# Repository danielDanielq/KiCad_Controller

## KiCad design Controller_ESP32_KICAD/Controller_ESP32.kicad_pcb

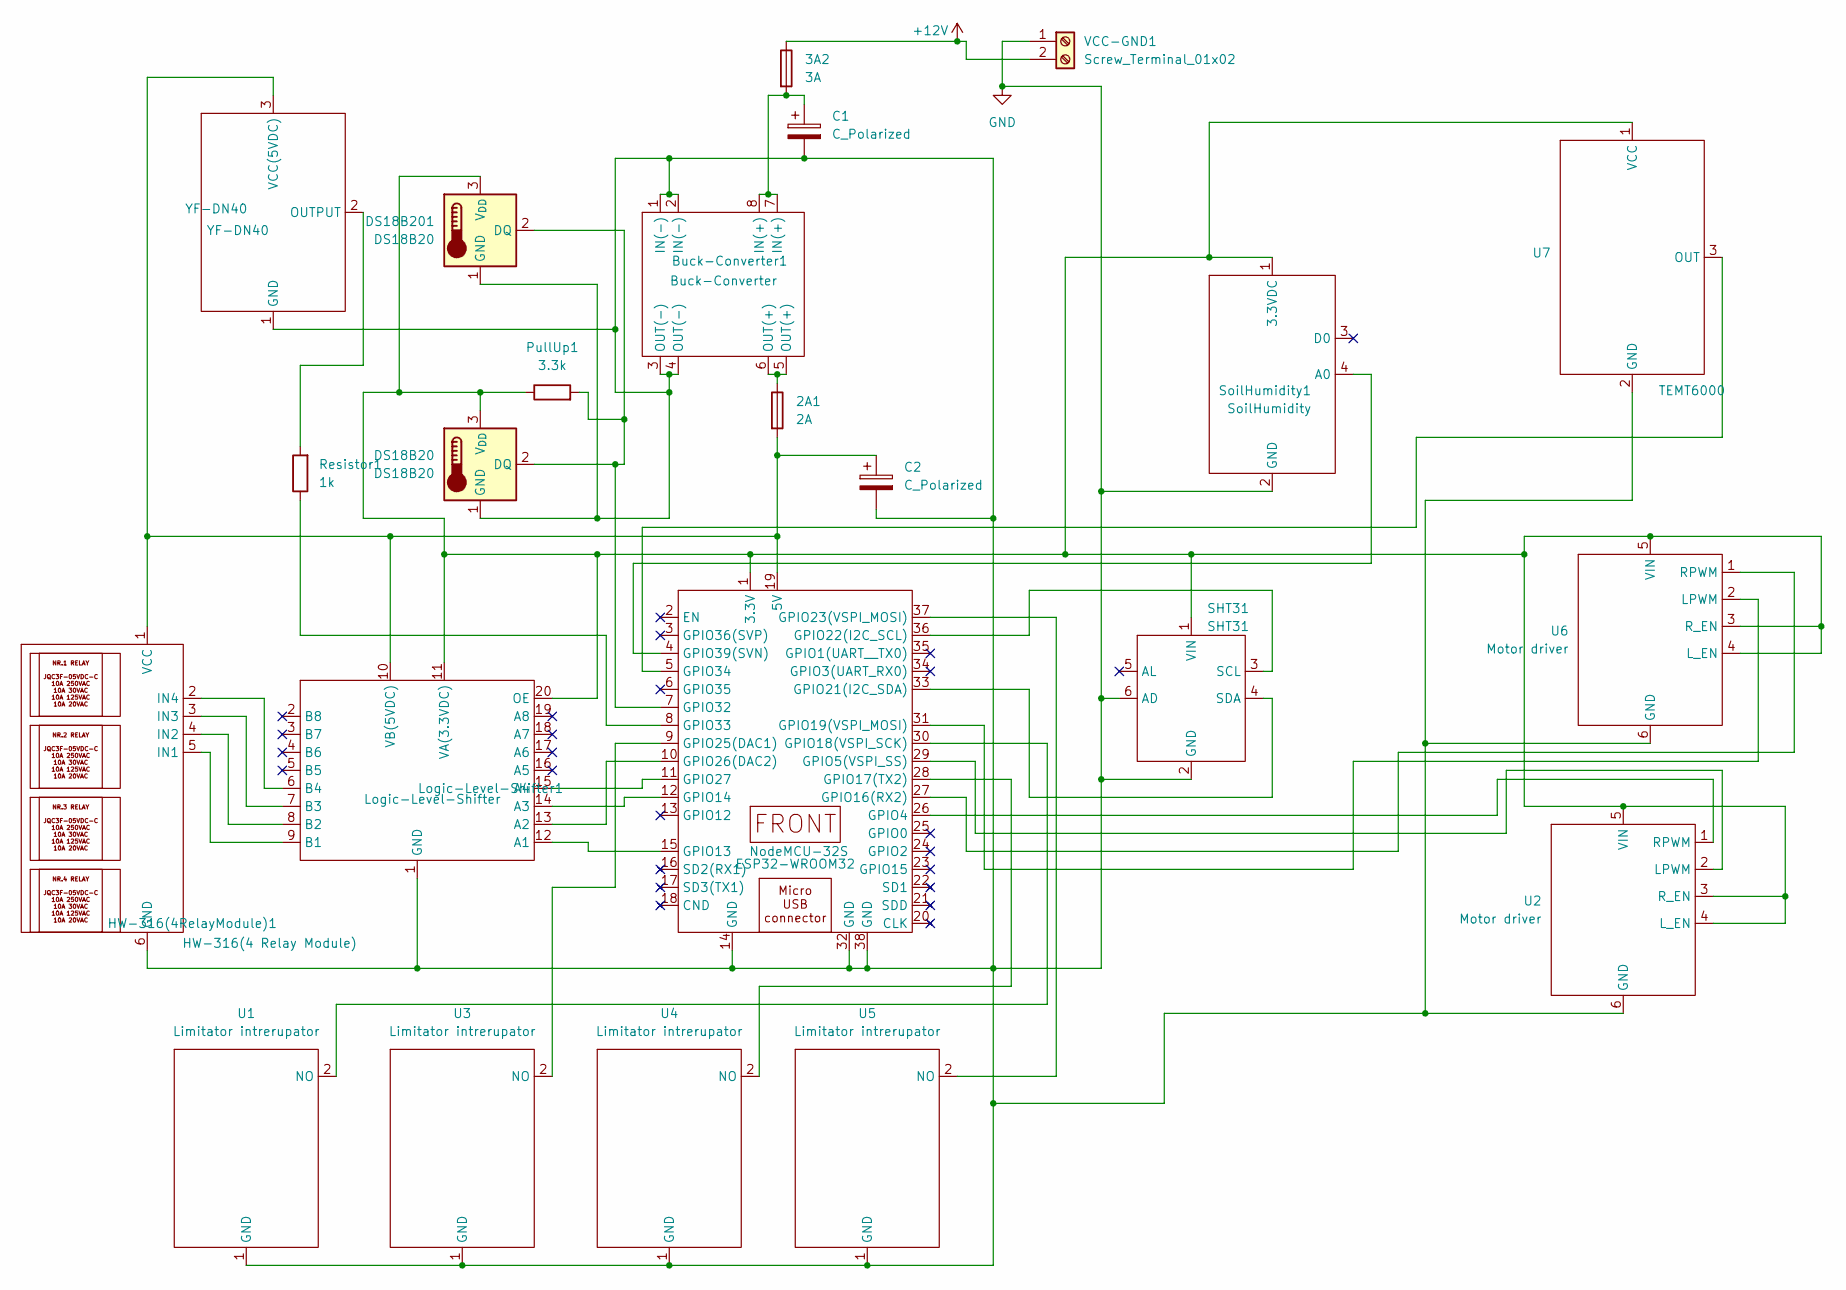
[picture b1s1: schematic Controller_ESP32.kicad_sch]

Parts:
2A1: 2A; M5X20MM Fuse
3A2: 3A; M5X20MM Fuse
Buck-Converter1: Buck-Converter; Buck Converter
C1, C2: C_Polarized; 1000uF Electrolytic Capacitator
DS18B20, DS18B201: DS18B20; JST_EH_B3B-EH-A_1x03_P2.50mm_Vertical
ESP32-WROOM32: NodeMCU-32S; ESP32-WROOM-32 DEVKIT V1 19PINS
HW-316(4RelayModule)1: HW-316(4 Relay Module); JST_EH_B6B-EH-A_1x06_P2.50mm_Vertical
Logic-Level-Shifter1: Logic-Level-Shifter; Logic Level Converter
PullUp1: 3.3k; R_Axial_DIN0207_L6.3mm_D2.5mm_P7.62mm_Horizontal
Resistor1: 1k; R_Axial_DIN0207_L6.3mm_D2.5mm_P7.62mm_Horizontal
SHT31: SHT31; JST_EH_B6B-EH-A_1x06_P2.50mm_Vertical
SoilHumidity1: SoilHumidity; PinHeader_1x04_P2.54mm_Vertical
U1, U3, U4, U5: Limitator intrerupator; JST_EH_B2B-EH-A_1x02_P2.50mm_Vertical
U2, U6: Motor driver; JST_EH_B6B-EH-A_1x06_P2.50mm_Vertical
U7: TEMT6000; JST_EH_B3B-EH-A_1x03_P2.50mm_Vertical
VCC-GND1: Screw_Terminal_01x02; TerminalBlock_MaiXu_MX126-5.0-02P_1x02_P5.00mm
YF-DN40: YF-DN40; JST_EH_B3B-EH-A_1x03_P2.50mm_Vertical

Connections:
+12V: 3A2.1, VCC-GND1.2
GND: Buck-Converter1.1 (IN(-)), Buck-Converter1.2 (IN(-)), Buck-Converter1.3 (OUT(-)), Buck-Converter1.4 (OUT(-)), C1.2, C2.2, DS18B20.1 (GND), DS18B201.1 (GND), ESP32-WROOM32.14 (GND), ESP32-WROOM32.32 (GND), ESP32-WROOM32.38 (GND), HW-316(4RelayModule)1.6 (GND), Logic-Level-Shifter1.1 (GND), SHT31.2 (GND), SHT31.6 (AD), SoilHumidity1.2 (GND), U1.1 (GND), U2.6 (GND), U3.1 (GND), U4.1 (GND), U5.1 (GND), U6.6 (GND), U7.2 (GND), VCC-GND1.1, YF-DN40.1 (GND)
unnamed: 2A1.1, Buck-Converter1.5 (OUT(+)), Buck-Converter1.6 (OUT(+))
unnamed: 3A2.2, Buck-Converter1.7 (IN(+)), Buck-Converter1.8 (IN(+)), C1.1
unnamed: DS18B20.2 (DQ), DS18B201.2 (DQ), ESP32-WROOM32.7 (GPIO32), PullUp1.2
unnamed: DS18B20.3 (V_{DD}), DS18B201.3 (V_{DD}), ESP32-WROOM32.1 (3.3V), Logic-Level-Shifter1.11 (VA(3.3VDC)), Logic-Level-Shifter1.20 (OE), PullUp1.1, SHT31.1 (VIN), SoilHumidity1.1 (3.3VDC), U2.3 (R_EN), U2.4 (L_EN), U2.5 (VIN), U6.3 (R_EN), U6.4 (L_EN), U6.5 (VIN), U7.1 (VCC)
unnamed: 2A1.2, C2.1, ESP32-WROOM32.19 (5V), HW-316(4RelayModule)1.1 (VCC), Logic-Level-Shifter1.10 (VB(5VDC)), YF-DN40.3 (VCC(5VDC))
unnamed: ESP32-WROOM32.26 (GPIO4), U2.1 (RPWM)
unnamed: ESP32-WROOM32.29 (GPIO5(VSPI_SS)), U2.2 (LPWM)
unnamed: ESP32-WROOM32.15 (GPIO13), Logic-Level-Shifter1.12 (A1)
unnamed: ESP32-WROOM32.12 (GPIO14), Logic-Level-Shifter1.14 (A3)
unnamed: ESP32-WROOM32.27 (GPIO16(RX2)), U6.1 (RPWM)
unnamed: ESP32-WROOM32.28 (GPIO17(TX2)), U4.2 (NO)
unnamed: ESP32-WROOM32.30 (GPIO18(VSPI_SCK)), U1.2 (NO)
unnamed: ESP32-WROOM32.31 (GPIO19(VSPI_MOSI)), U6.2 (LPWM)
unnamed: ESP32-WROOM32.33 (GPIO21(I2C_SDA)), SHT31.4 (SDA)
unnamed: ESP32-WROOM32.36 (GPIO22(I2C_SCL)), SHT31.3 (SCL)
unnamed: ESP32-WROOM32.37 (GPIO23(VSPI_MOSI)), U5.2 (NO)
unnamed: ESP32-WROOM32.9 (GPIO25(DAC1)), U3.2 (NO)
unnamed: ESP32-WROOM32.10 (GPIO26(DAC2)), Logic-Level-Shifter1.13 (A2)
unnamed: ESP32-WROOM32.11 (GPIO27), Logic-Level-Shifter1.15 (A4)
unnamed: ESP32-WROOM32.8 (GPIO33), Resistor1.1
unnamed: ESP32-WROOM32.5 (GPIO34), U7.3 (OUT)
unnamed: ESP32-WROOM32.4 (GPIO39(SVN)), SoilHumidity1.4 (A0)
unnamed: HW-316(4RelayModule)1.5 (IN1), Logic-Level-Shifter1.9 (B1)
unnamed: HW-316(4RelayModule)1.4 (IN2), Logic-Level-Shifter1.8 (B2)
unnamed: HW-316(4RelayModule)1.3 (IN3), Logic-Level-Shifter1.7 (B3)
unnamed: HW-316(4RelayModule)1.2 (IN4), Logic-Level-Shifter1.6 (B4)
unnamed: Resistor1.2, YF-DN40.2 (OUTPUT)

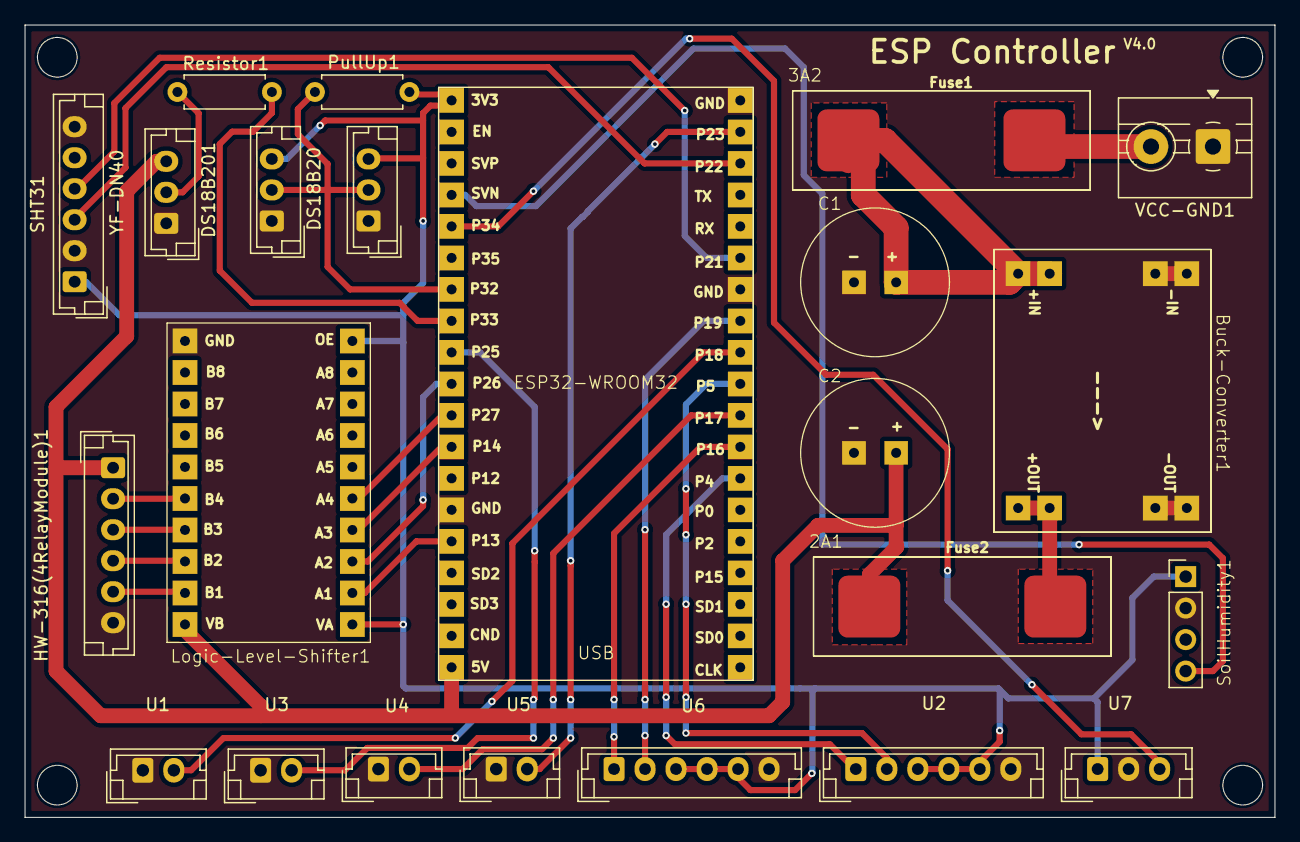
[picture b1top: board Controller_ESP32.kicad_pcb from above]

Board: 4 copper layers, 100.8 x 63.9 mm, 23 parts (0 on the bottom side), 29 nets.

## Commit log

2025-06-16 Update LICENSE
